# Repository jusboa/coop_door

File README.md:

# coop_door

Chicken coop door that opens and closes based on daylight. A photoresistor detects daylight and a DC motor operates the door. The software runs on a battery-powered Raspberry Pi Pico using MicroPython.

## Host development

Install [uv](https://docs.astral.sh/uv/), then set up the test and lint tools:

```sh
uv sync --locked --no-default-groups --group test --group lint
uv run --locked --group test pytest
uv run --locked --group lint flake8 . --exclude=.env,.venv --count --select=E9,F63,F7,F82 --show-source --statistics
uv run --locked --group lint flake8 . --exclude=.env,.venv --count --exit-zero --max-complexity=10 --max-line-length=127 --statistics
uv run --locked --group lint pylint $(git ls-files '[^tests]*.py')
```

## Deploy

Connect the Pico, then run the deployment script from the repository root:

```sh
uv run --locked --no-default-groups --group deploy bash install.sh
```

The script uses `mpremote` from the deployment dependency group to copy the MicroPython files and install the device-side `logging` module with MIP. `mip` is run on the device; it is not a host dependency.

The project intentionally uses uv's non-package mode: the MicroPython application is copied to the device, not installed as a host Python package.

Regenerate and commit `uv.lock` after dependency or metadata changes with `uv lock`.

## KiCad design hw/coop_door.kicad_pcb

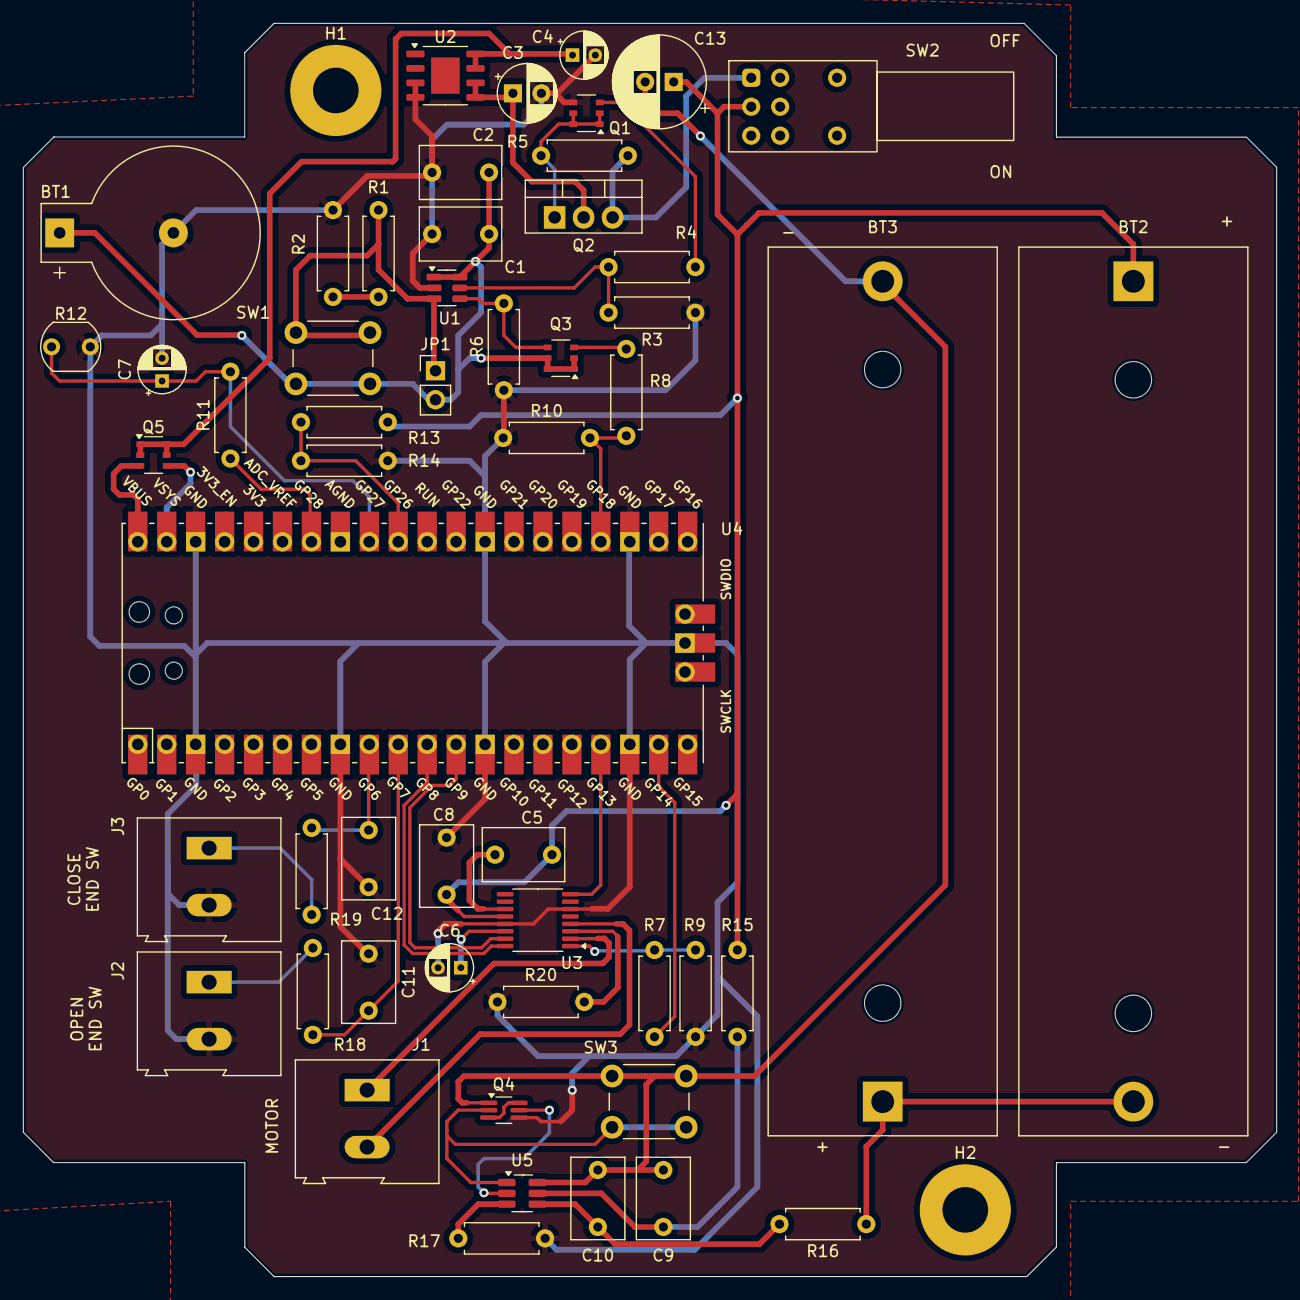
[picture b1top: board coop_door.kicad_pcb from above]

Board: 2 copper layers, 110.0 x 110.0 mm, 55 parts (0 on the bottom side), 41 nets.

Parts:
BT1: CR1220; BatteryHolder_Keystone_500
BT2, BT3: Battery_Cell; BatteryHolder_MPD_BH-18650-PC2
C1, C9, C10: 0.1u; C_Rect_L7.0mm_W4.5mm_P5.00mm
C2, C8: 10u; C_Rect_L7.0mm_W4.5mm_P5.00mm
C3: 1u; CP_Radial_D5.0mm_P2.50mm
C4, C6: 2.2u; CP_Radial_D4.0mm_P2.00mm
C5: 10n; C_Rect_L7.0mm_W4.5mm_P5.00mm
C7: 4.7u; CP_Radial_D4.0mm_P2.00mm
C11, C12: 2.2u; C_Rect_L7.0mm_W4.5mm_P5.00mm
C13: 680u; CP_Radial_D8.0mm_P2.50mm
H1, H2: MountingHole; MountingHole_4mm_Pad
J1, J2, J3: Screw_Terminal_01x02; TerminalBlock_Altech_AK300-2_P5.00mm
JP1: Jumper_2_Open; PinHeader_1x02_P2.54mm_Vertical
Q1, Q3: IRLTS6342; TSOP-6_1.65x3.05mm_P0.95mm
Q2: IRF4905; TO-220-3_Vertical
Q4: BSD235NH; SOT-363_SC-70-6_Handsoldering
Q5: BSL207SPH; TSOP-6_1.65x3.05mm_P0.95mm
R1, R2: 47k; R_Axial_DIN0207_L6.3mm_D2.5mm_P7.62mm_Horizontal
R3, R6: 51k; R_Axial_DIN0207_L6.3mm_D2.5mm_P7.62mm_Horizontal
R4, R7, R8: 1k; R_Axial_DIN0207_L6.3mm_D2.5mm_P7.62mm_Horizontal
R5, R9, R10, R11: 10k; R_Axial_DIN0207_L6.3mm_D2.5mm_P7.62mm_Horizontal
R12: GL5516; R_LDR_5.1x4.3mm_P3.4mm_Vertical
R13: 15k; R_Axial_DIN0207_L6.3mm_D2.5mm_P7.62mm_Horizontal
R14, R18, R19: 5k; R_Axial_DIN0207_L6.3mm_D2.5mm_P7.62mm_Horizontal
R15, R16: 470; R_Axial_DIN0207_L6.3mm_D2.5mm_P7.62mm_Horizontal
R17: 2k; R_Axial_DIN0207_L6.3mm_D2.5mm_P7.62mm_Horizontal
R20: 0R68; R_Axial_DIN0207_L6.3mm_D2.5mm_P7.62mm_Horizontal
SW1, SW3: SW_Push; SW_PUSH_6mm
SW2: SW_DPDT_x2; Double_Toggle_Switch_8Pins_THT_H10mm_W9mm_L24mm_Vertical
U1: TPL5111; SOT-23-6
U2: TPS76633; SOIC-8-1EP_3.9x4.9mm_P1.27mm_EP2.514x3.2mm
U3: DRV8833PW; TSSOP-16_4.4x5mm_P0.65mm
U4: Pico; RPi_Pico_SMD_TH
U5: S-8252; SOT-23-6_Handsoldering

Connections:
+BATT: BT2.1 (+), C5.1, C8.2, C13.1, R13.1, R15.1, SW2.2 (B), U3.12 (VM)
/VBUS: Q5.3 (G), U4.40 (VBUS)
/VIN: C3.1, Q2.2 (D), U2.5 (IN), U2.6 (IN)
/VSYS: Q5.4 (S), U4.39 (VSYS)
/battery_sense: R13.2, R14.1, U4.31 (GPIO26_ADC0)
/close_end_switch: C12.1, R19.1, U4.9 (GPIO6)
/done: R8.1, R10.2, U4.24 (GPIO18)
/light_sense: C7.1, R11.2, R12.1, U4.32 (GPIO27_ADC1)
/light_sense_control: R11.1, U4.34 (GPIO28_ADC2)
/motor_drv_AIN1: U3.16 (AIN1), U4.11 (GPIO8)
/motor_drv_AIN2: U3.15 (AIN2), U4.12 (GPIO9)
/motor_drv_AISEN: R20.2, U3.3 (AISEN)
/motor_drv_AOUT1: J1.1, U3.2 (AOUT1)
/motor_drv_AOUT2: J1.2, U3.4 (AOUT2)
/motor_drv_nFAULT: U3.8 (nFAULT), U4.17 (GPIO13)
/motor_drv_nSLEEP: R7.2, U4.19 (GPIO14)
/open_end_switch: C11.1, R18.1, U4.10 (GPIO7)
/power_control: R3.2, R4.2, U1.5 (~DRV)
GND: BT1.2 (-), C1.2, C2.2, C3.2, C4.2, C6.2, C7.2, C8.1, C11.2, C12.2, J2.2, J3.2, Q1.4 (S), Q4.4 (S), R2.1, R3.1, R6.1, R9.2, R10.1, R12.2, R14.2, R17.2, R20.1, U1.2 (GND), U2.3 (GND), U2.4 (nEN), U3.6 (BISEN), U3.13 (GND), U4.3 (GND), U4.8 (GND), U4.13 (GND), U4.18 (GND), U4.23 (GND), U4.28 (GND), U4.38 (GND), U4.42 (GND)
unnamed: BT2.2 (-), BT3.1 (+), R16.1
unnamed: BT3.2 (-), C9.2, C10.2, C13.2, Q4.1 (S), SW3.1, U5.6 (VSS)
unnamed: J2.1, R18.2
unnamed: J3.1, R19.2
unnamed: JP1.1 (A), R1.2, SW1.1, U1.3 (DELAY/M_DRV)
unnamed: Q1.3 (G), R4.1
unnamed: Q1.1 (D), Q1.2 (D), Q1.5 (D), Q1.6 (D), Q2.1 (G), R5.2
unnamed: Q2.3 (S), R5.1, SW2.1 (A)
unnamed: Q3.3 (G), R8.2
unnamed: Q3.4 (S), R6.2, U1.4 (DONE)
unnamed: Q4.3 (D), Q4.6 (D)
unnamed: Q4.2 (G), SW3.2, U5.1 (DO)
unnamed: Q4.5 (G), U5.2 (CO)
unnamed: R1.1, R2.2
unnamed: C5.2, U3.11 (VCP)
unnamed: C6.1, U3.14 (VINT)
unnamed: R7.1, R9.1, U3.1 (nSLEEP)
unnamed: C10.1, R16.2, U5.4 (VC)
unnamed: C9.1, R15.2, U5.5 (VDD)
unnamed: R17.1, U5.3 (VM)
VCC: C4.1, Q5.1 (D), Q5.2 (D), Q5.5 (D), Q5.6 (D), U2.7 (OUT), U2.8 (OUT)
VDD: BT1.1 (+), C1.1, C2.1, JP1.2 (B), Q3.1 (D), Q3.2 (D), Q3.5 (D), Q3.6 (D), SW1.2, U1.1 (VDD), U1.6 (EN/ONE_SHOT)

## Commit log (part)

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2023-11-20 Adding first draft for dcmotor drive, end_switch drive, light sensor and task scheduler
2023-11-20 Renaming src to scoop_door for better package reference.
2023-11-21 Adding an empty test file. Moving
2023-11-21 Adding __init__ to access modules via dot notation.
2023-11-22 Changing the repository structure.
    Adding __init__ to make module dot reference possible.
    Moving application code into a separate folder.
    Adding first draft of a dcmotor test.
2023-11-22 Adding first few meaningful dcmotor tests.
2023-11-22 Remove code leftovers.
2023-11-23 Adding more motor tests.
2023-11-23 is_running rather than is_off
2023-11-27 Adding requirements.txt
2023-11-28 Removing pkg-resources since it failed the github build.
2024-08-19 Unit test for end_switch
2024-08-19 Removing unused packages
2024-08-19 Lately removed packages are actually needed by pytest
2024-08-26 Use pytest way for end_switch tests
2024-08-26 Use pytest way for dc_motor tests
2024-08-27 Adding a digital filter
2024-08-27 Ignore virtual environment folder
2024-10-15 Starting a statemachine.
2024-10-18 * More business logic * Use callback to get state of switches and day/night
2024-10-19 Test observer slots.
2024-10-23 Add light sensor tests.
2024-12-05 Add a simple state machine
2024-12-06 Handle properly direct transition from/into a nested state
2024-12-06 Use == to compare constant strings
2024-12-09 Add time limited state.
2024-12-09 Timer needs to be started on a state entry,
    simplify hierarchy dealing.
2024-12-09 state start does not need to return anything
2024-12-09 Use built in function to revrse the list
2024-12-09 Use custom state machine class.
2024-12-14 Add timer test
    Update light sensor resistances to match actual values.
    Update GPIO pins and ADC channel to match actual schematics.
2024-12-14 Fix wrong import in timer.
    Fix timer callback, it needs to take a timer object as its argument.
2024-12-14 Update tests to match the timer callback.
2024-12-14 Read light periodically.
    Test the HW wiring (pins and ADC channel).
2024-12-15 Periodically refresh end switches.
    State machine needs to use single shot timer for state timeout.
    Disable logging since it is not in micropython libs.
2024-12-15 Add main
2024-12-15 Stop the timer on exit.
    When day comes while closing the door, open it. When night comes while opening the door, close it.
2024-12-23 Power saving #1
    Disable motor driver when idled.
    Disable light sensor when idled.
    Determin only bistate of light sensor -> day/night to avoid erroneous light scaling.
2025-01-16 Update light sensor HW
    Update pin - control pin is GPIO0.
    Update resistance to match new light sensor circuit. Rup = 10e3, sensor = GL5516.
2025-01-26 End switch revised
    * Remap end switches pins
    * Use interrupt to detect end switch state
2025-01-26 Update unit tests
2025-01-26 State machine refactoring
    * Add a state diagram
    * Restructure with super states - day and night
2025-02-03 Take out switches out of periodic refresh
    * No need to ask periodically what the switches state is. They trigger external gpio interrupt on change.
    * Give signals a name
    * Use choice to decide on switch state on power up
2025-02-07 Make motor direction a parameter
2025-02-07 Separate state machines
    Separate motor control from high level business logic.
2025-02-09 reverse motor rotation
    * On stuck start switch reverse the motor direction
    * efactor tests to exploit fixtures more
2025-02-10 Limit number of detach trials
2025-02-11 Simplify state choice
2025-02-11 Remove the recursion
    Refactor state transition to get rid of the recursion. Simplify the code.
2025-02-13 New HW update
    * Pin remapping
    * door controller needs to be started
    * Fix wrong switch mapping
    * Extend door drive timeouts
    * Detect both switch events - open and close
    * Fix trials limit
2025-02-14 Save energy
    * Sleep after door close/open
    * Flatten the code by using signal stack not to exceeed the stack
2025-02-15 Update tests to the signal stack
2025-02-22 Improve light sensor robustness
    * Add cap to filter signal - add seonsor startup delay to let the cap charge.
    * Increase light sensor hysteresis.
    * Refresh inputs less often - just once per 100ms is enough.
2025-02-22 Toggle sleep pin0
    Generate a 500Hz/50% PWM on sleep pin when going to sleep for the TPL5110 not to miss it. Sometimes it did not catch it and then it remained awaik until next cycle.
2025-02-23 Add battery voltage reading
2025-02-28 Duty cycle the motor
    * Drive the motor with PWM based on input voltage.
    * ADC fixed. It actually need to be either initialized with pin object or the corresponding pin needs to be set as input
    otherwise it's wrongly configured and gives wrong reading!
2025-02-28 Tune day/night threshold
    Aftre the ADC pin configuration fix the day threshold had to be retuned.
2025-03-01 Fine tune the motor drive
    * The best frequency seems to be 10 kHz. It filters well the dc component. It does not give any noise.
    * Power supply voltage is actually a bit less than 3.3 V -> typically 3.2 V.
    * Modify the battery sensing voltage divider to be able to measure up to 12V, when motor shall not be driven.
2025-03-02 Revise tests
    * Fixing tests that reacted on motor detach state rather than the go state.
    * Associate door drive timeout with go state.
2025-03-30 Use standard logging
2025-04-02 install script + freq
    Add installation script.
    Lower the CPU frequency to save power.
2025-04-03 f -> 18MHz
    Going down with clock freq to 18MHz. The lower value is not possible with micropython.
2025-04-07 freq up, global logging settings
    Increase the clock rate since somehow the usb console does not work reliably.
    Setup logging globally in main.py.
2025-04-07 debug -> info for welcome message
2025-04-09 log to console & file
    Add file logging.
    Change log formatter to show time from the start.
    f->18MHz, the USB connection problem is most likely not due to clock freq.
2025-04-10 Update motor driver sleep
    Update the drv8833 sleep gpio.
    f back to 48MHz. It really is due to low clock frequency that the USB connection is not reliable.
2025-04-16 lightsleep
    Investigated lightsleep option while motor runs. But no, timers stop to do PWM.
    Got rid of some too frequent debug messages that overwhelmed the log.
2025-06-30 Add HW
    * Schematics
    * PCB
    * Project footprints
2025-07-24 Revise PCB dimensions
    * Add project specific symbol library
    * Change PCB dimensions to fit the housing
    * Move some components for the connectors to be easily accessible
2025-08-14 V-regulator
    Use a correct symbol and package for TPS76633 voltage regulator.
2025-08-18 Transitor types
    Show transitor types in the schematics
2025-08-25 Battery terminals
    Adding labels +/- to battery holders.
2025-08-26 PCB fixes
    - Fix the battery protection IC MOSFET connections
    - Add the main switch ON/OFF silkscreen labels
2025-08-26 Termials labels
    Add labels to end switch and motor terminals.
2025-08-26 Update venv
    - Update venv packages
    - Fix some wrong test assertions
2025-08-26 Update pinout
    Update pinout to the new PCB
2025-08-28 Fix C13
    Fix the schematics - C13 needs to be connected accross the battery, otherwise U5 detects voltage drop when motor starts and shuts the device down.
2025-11-10 Update schematics&PCB
    - Add button to start the battery protection IC
    - Add motor resitor to AISEN pin to limit the current to ~300mA
2026-01-03 Recover the original repository from zip file
2026-01-03 Add gitignore
2026-01-03 Add hw submodule
2026-01-04 pylint, tests
    - Rework to lessen pylint warnings.
    - Fix wrong uni tests assertions
    - Remove unused package
2026-01-04 Remove unused package
2026-01-04 Fixing also main for pylint
2026-01-04 Exclude tests from pylint
2026-01-04 Cure/ignore the rest of pylint findings.
2026-01-04 Get rid of more pylint findings
2026-01-04 Test with python 3.12
2026-01-04 Fix the pinout
2026-01-05 Fix string format, fix import error, ignore emacs temps
